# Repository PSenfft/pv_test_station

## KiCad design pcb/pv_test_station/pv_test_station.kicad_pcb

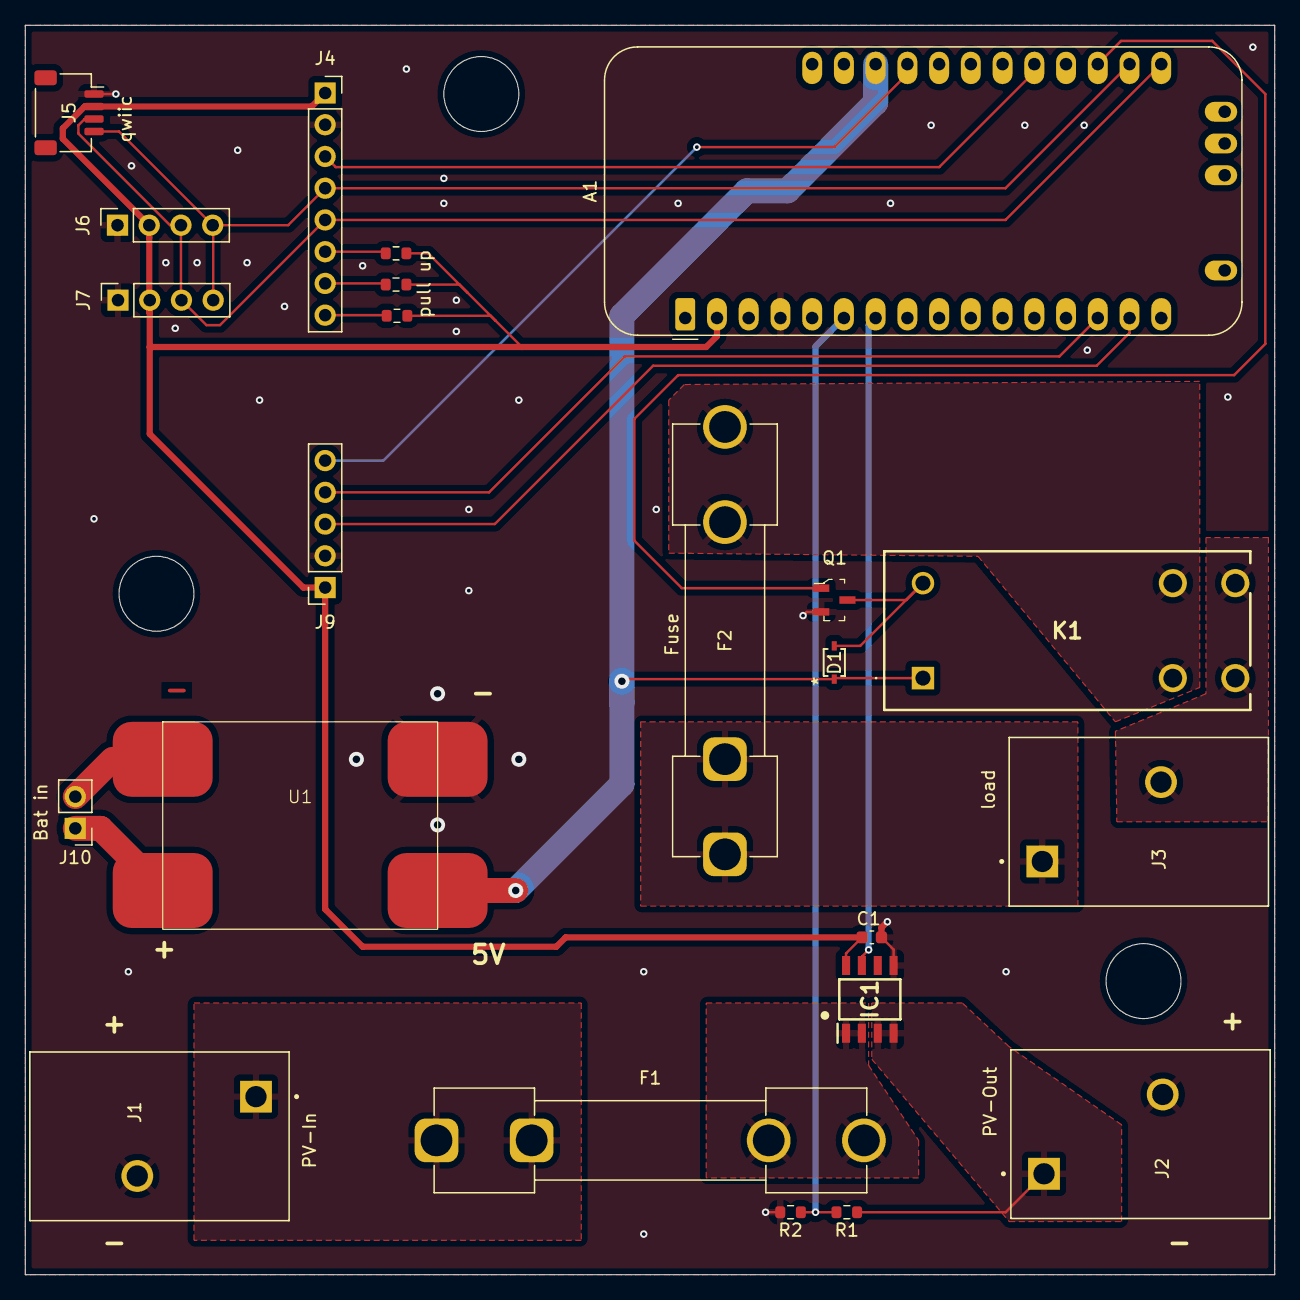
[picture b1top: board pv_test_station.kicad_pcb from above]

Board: 2 copper layers, 100.0 x 100.0 mm, 23 parts (0 on the bottom side), 24 nets.

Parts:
A1: Adafruit_Feather_M0_RFM9x_LoRa_Radio; Adafruit_Feather_M0_RFM
C1: 1uF; C_0603_1608Metric
D1: D; DIODE_BAR6303WE6327HTSA1_INF
F1, F2: Fuse; Fuseholder_Clip-6.3x32mm_Littelfuse_102_Inline_P34.21x7.62m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
IC1: CT426-HSN830DR; SOIC127P600X172-8N
J1: PV-In; PHOENIX_1017521
J2: PV-Out; PHOENIX_1017521
J3: load; PHOENIX_1017521
J4: FRAM; PinSocket_1x08_P2.54mm_Vertical
J5: qwiic; JST_SH_SM04B-SRSS-TB_1x04-1MP_P1.00mm_Horizontal
J6: Temp1; PinSocket_1x04_P2.54mm_Vertical
J7: Temp2; PinSocket_1x04_P2.54mm_Vertical
J9: GPS; PinSocket_1x05_P2.54mm_Vertical
J10: Bat in; PinHeader_1x02_P2.54mm_Vertical
K1: AZ576-1A-12DE; AZ5761A12DE
Q1: 2N7002; SOT-23-3
R1: 100k; R_0603_1608Metric
R2: 8,33k; R_0603_1608Metric
R3, R4, R5: nc; R_0603_1608Metric
U1: DCDC

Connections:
+3.3V: A1.2 (3V3), C1.2, IC1.8 (VDD), J4.1, J5.2, J6.2, J7.2, J9.1, R3.2, R4.2, R5.2
+5V: A1.26 (USB), D1.1 (K), K1.1 (COIL_1), U1.4 (Vo+)
/+ In: F1.1, J1.1
/+ Out: IC1.3 (IP-_1), IC1.4 (IP-_2), J2.1, R1.1
/A_meter: A1.7 (A2), IC1.7 (OUT)
/PPS: A1.25 (D13), J9.5
/RX: A1.15 (TX/D1), J9.3
/RelaisPin: A1.19 (D5), Q1.1 (G)
/SCL: A1.18 (SCL/D21), J4.4, J5.4, J6.4, J7.4
/SDA: A1.17 (SDA/D20), J4.5, J5.3, J6.3, J7.3
/TX: A1.14 (RX/D0), J9.4
/V_meter: A1.6 (A1), R1.2, R2.1
/WP: A1.21 (D9), J4.3
GND: A1.4 (GND), C1.1, IC1.5 (GND), J1.2, J2.2, J4.2, J5.1, J6.1, J7.1, J9.2, Q1.2 (S), R2.2, U1.3 (Vo-)
unnamed: D1.2 (A), K1.2 (COIL_2), Q1.3 (D)
unnamed: F1.2, IC1.1 (IP+_1), IC1.2 (IP+_2)
unnamed: J3.2, K1.5 (NO_1), K1.8 (NO_2)
unnamed: J4.6, R3.1
unnamed: J4.7, R4.1
unnamed: J4.8, R5.1
unnamed: J10.1, U1.2 (Vi+)
unnamed: J10.2, U1.1 (Vi-)
unnamed: F2.2, K1.4 (COM_1), K1.7 (COM_2)
relais: F2.1, J3.1

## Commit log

2024-07-17 Create LICENCE
2024-07-17 Rename partlist.md to partslist.md
2024-08-19 added doc dir
2024-09-10 create prject for dataminer
2024-09-13 added Temp sensor lib
2024-09-19 added python script for db_station
2024-09-25 devide main file in more different files; added isr and time scructs
2024-09-25 add sequence diagram
2024-09-25 added sequence_diagram.svg
2024-09-27 working on timer
2024-09-27 Adafruit Zerotimer is not supported. switch to other library
2024-10-01 restructured code
2024-10-04 something doesnt work with temp sensor
2024-10-11 experimenting with code
2024-10-11 edit sequence diagram
2024-10-11 created pcb
2024-10-14 reading temp sensor is working
2024-10-14 Update requirements.md
    switch partlist to own file
2024-10-14 Rename partslist.md to doc/partslist.md
2024-10-14 working on wait or sleep method
2024-10-15 working on gps ppt backup
2024-10-15 main function is finish with dummy measurement
2024-10-15 measurement works
2024-10-16 protocol seems to work. alternative pps signal from rtc is needed
2024-10-16 timnestampo and timestamp from protocol doesnt fit
2024-10-16 change protocol to 16bit each
2024-10-16 protocol works and can be sended over lora. db script loads something in influx, but doesnt work perfekt
2025-01-10 finished pcb
2025-01-11 fixed some PCB issues (resistor size, GND on top layer)
2025-01-12 Update PV_test_station.drawio
    Added Grafana in drawio file
2025-01-16 added docker for db
2025-01-16 made some fixes
2025-01-16 made some fixes in db writer_mariaDB
2025-01-16 made some fixes in db
2025-01-17 last fixes before presentation
2025-01-20 changed endianess in protocol
2025-01-20 changed some kicad files
